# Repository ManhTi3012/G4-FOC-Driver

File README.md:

# ⚠️ **WARNING: PROJECT UNDER DEVELOPMENT, CHANGES WILL BE MADE**

# G4-FOC-Driver

# Liability
* The software and hardware are still in development and may contain bugs, errors, or incomplete features.
* Users are encouraged to use this software and hardware responsibly and at their own risk.

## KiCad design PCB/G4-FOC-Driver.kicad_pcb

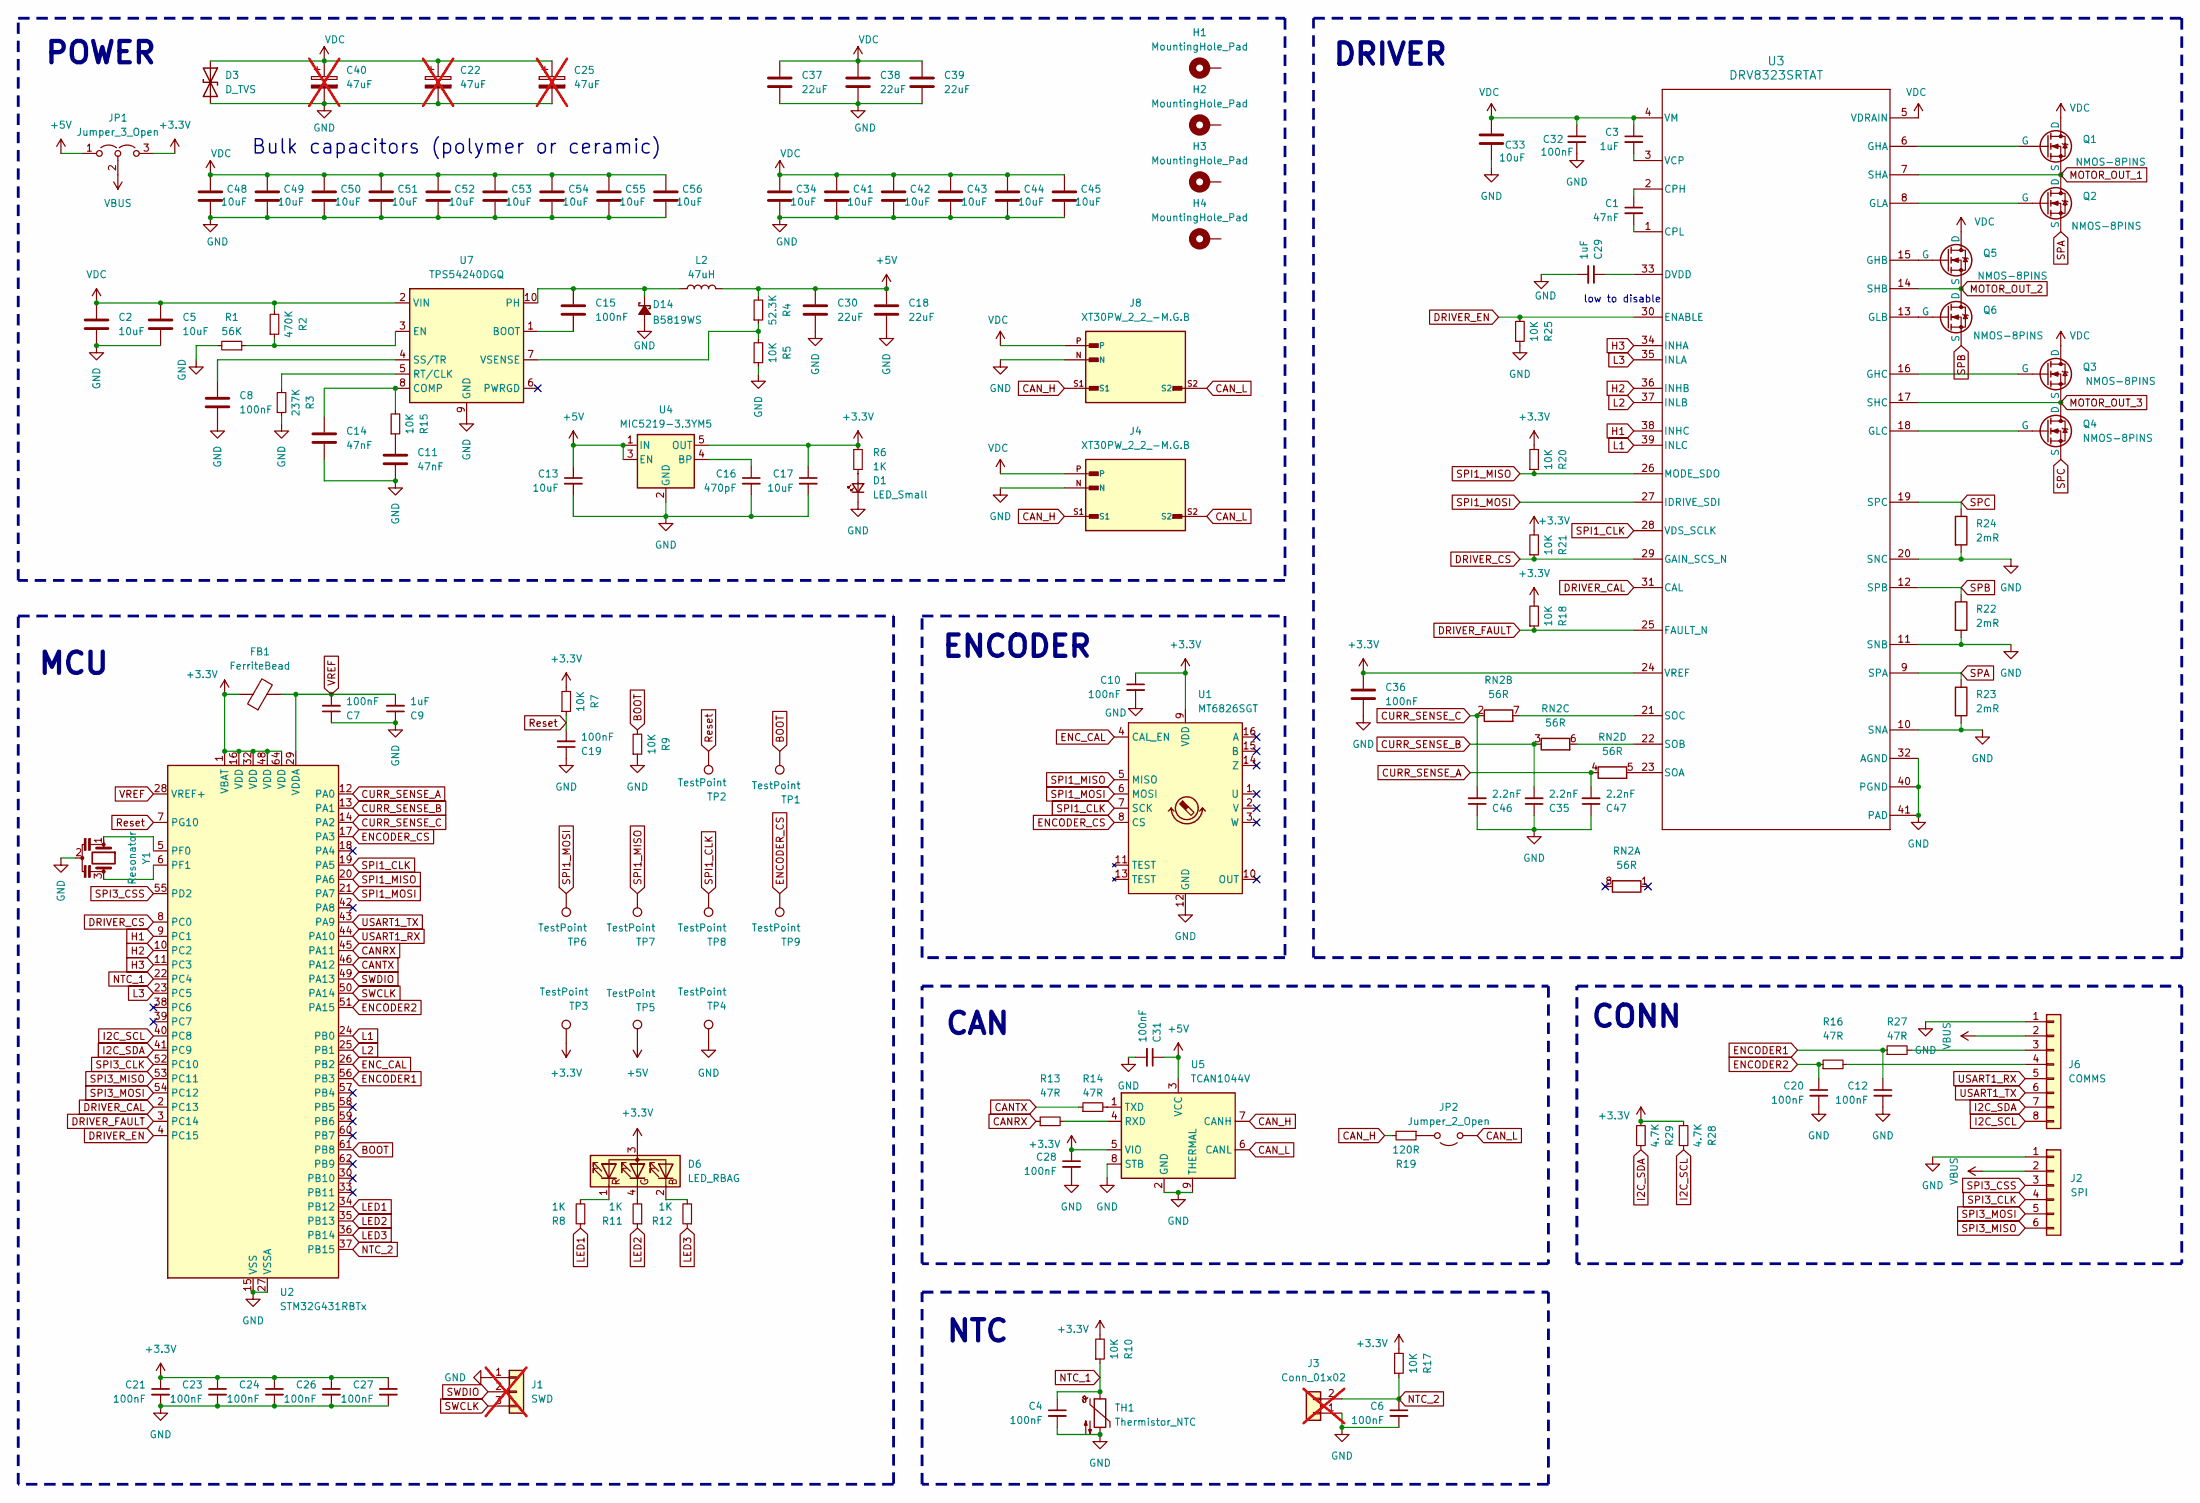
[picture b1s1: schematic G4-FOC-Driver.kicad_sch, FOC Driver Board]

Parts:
C1, C11, C14: 47nF; C_0603_1608Metric
C2, C5, C33, C34, C41, C42, C43, C44, C45, C48, C49, C50, C51, C52, C53, C54, C55, C56: 10uF; C_1206_3216Metric
C3, C9, C29: 1uF; C_0603_1608Metric
C4, C6, C7, C8, C10, C12, C15, C19, C20, C21, C23, C24, C26, C27, C28, C31, C32, C36: 100nF; C_0603_1608Metric
C13, C17: 10uF; C_0603_1608Metric
C16: 470pF; C_0603_1608Metric
C18, C30, C37, C38, C39: 22uF; C_0805_2012Metric
C22, C25, C40: 47uF; CP_Elec_6.3x5.9; not fitted
C35, C46, C47: 2.2nF; C_0603_1608Metric
D1: LED_Small; LED_0603_1608Metric
D3: D_TVS; D_SMB
D6: LED_RBAG; LED_Cree-PLCC4_2x2mm_CW
D14: B5819WS; D_0805_2012Metric
FB1: FerriteBead; L_0603_1608Metric
H1, H2, H3, H4: MountingHole_Pad; MountingHole_3.2mm_M3_Pad_Via
J1: SWD; PinHeader_1x03_P2.54mm_Vertical; not fitted
J2: SPI; JST_GH_SM06B-GHS-TB_1x06-1MP_P1.25mm_Horizontal
J3: Conn_01x02; PinHeader_1x02_P2.00mm_Vertical; not fitted
J4, J8: XT30PW_2_2_-M.G.B; AMASS_XT30PW_2_2_-M.G.B; PARTREV NA
J6: COMMS; JST_GH_SM08B-GHS-TB_1x08-1MP_P1.25mm_Horizontal
JP1: Jumper_3_Open; SolderJumper-3_P1.3mm_Open_RoundedPad1.0x1.5mm
JP2: Jumper_2_Open; SolderJumper-2_P1.3mm_Open_RoundedPad1.0x1.5mm
L2: 47uH; L_APV_ANR4020
Q1, Q2, Q3, Q4, Q5, Q6: NMOS-8PINS; PQFN-8-EP_6x5mm_P1.27mm_Generic
R1: 56K; R_0603_1608Metric
R2: 470K; R_0603_1608Metric
R3: 237K; R_0603_1608Metric
R4: 52.3K; R_0603_1608Metric
R5, R7, R9, R10, R15, R17, R18, R20, R21, R25: 10K; R_0603_1608Metric
R6, R8, R11, R12: 1K; R_0603_1608Metric
R13, R14, R16, R27: 47R; R_0603_1608Metric
R19: 120R; R_0603_1608Metric
R22, R23, R24: 2mR; R_2512_6332Metric
R28, R29: 4.7K; R_0603_1608Metric
RN2: 56R; R_Array_Convex_4x0402
TH1: Thermistor_NTC; R_0603_1608Metric
TP1, TP2, TP3, TP4, TP5, TP6, TP7, TP8, TP9: TestPoint; TestPoint_Pad_D1.0mm
U1: MT6826SGT; TSSOP-16_4.4x5mm_P0.65mm
U2: STM32G431RBTx; LQFP-64_10x10mm_P0.5mm
U3: DRV8323SRTAT; RTA0040B
U4: MIC5219-3.3YM5; SOT-23-5
U5: TCAN1044V; Texas_S-PVSON-N8_ThermalVias
U7: TPS54240DGQ; HVSSOP-10-1EP_3x3mm_P0.5mm_EP1.57x1.88mm_ThermalVias
Y1: Resonator; Resonator_SMD_Murata_CSTxExxV-3Pin_3.0x1.1mm

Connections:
+3.3V: C10.1, C17.1, C21.1, C23.1, C24.1, C26.1, C27.1, C28.1, C36.1, D6.3 (A), FB1.1, JP1.3 (B), R6.1, R7.2, R10.2, R17.2, R18.2, R20.2, R21.2, R28.2, R29.2, TP3.1, U1.9 (VDD), U2.1 (VBAT), U2.16 (VDD), U2.32 (VDD), U2.48 (VDD), U2.64 (VDD), U3.24 (VREF), U4.5 (OUT), U5.5 (VIO)
+5V: C13.1, C18.2, C30.2, C31.1, JP1.1 (A), L2.2, R4.2, TP5.1, U4.1 (IN), U4.3 (EN), U5.3 (VCC)
BOOT: R9.2, TP1.1, U2.61 (PB8)
CANRX: R13.1, U2.45 (PA11)
CANTX: R14.1, U2.46 (PA12)
CAN_H: J4.S1, J8.S1, R19.2, U5.7 (CANH)
CAN_L: J4.S2, J8.S2, JP2.1 (A), U5.6 (CANL)
CURR_SENSE_A: C47.2, RN2.4 (R4.1), U2.12 (PA0)
CURR_SENSE_B: C35.2, RN2.3 (R3.1), U2.13 (PA1)
CURR_SENSE_C: C46.2, RN2.2 (R2.1), U2.14 (PA2)
DRIVER_CAL: U2.2 (PC13), U3.31 (CAL)
DRIVER_CS: R21.1, U2.8 (PC0), U3.29 (GAIN_SCS_N)
DRIVER_EN: R25.2, U2.4 (PC15), U3.30 (ENABLE)
DRIVER_FAULT: R18.1, U2.3 (PC14), U3.25 (FAULT_N)
ENCODER1: C12.1, R27.1, U2.56 (PB3)
ENCODER2: C20.1, R16.1, U2.51 (PA15)
ENCODER_CS: TP9.1, U1.8 (CS), U2.17 (PA3)
ENC_CAL: U1.4 (CAL_EN), U2.26 (PB2)
GND: C2.1, C4.2, C5.1, C6.2, C7.1, C8.1, C9.1, C10.2, C11.1, C12.2, C13.2, C14.1, C16.2, C17.2, C18.1, C19.1, C20.2, C21.2, C22.2, C23.2, C24.2, C25.2, C26.2, C27.2, C28.2, C29.2, C30.1, C31.2, C32.2, C33.1, C34.1, C35.1, C36.2, C37.1, C38.1, C39.1, C40.2, C41.1, C42.1, C43.1, C44.1, C45.1, C46.1, C47.1, C48.1, C49.1, C50.1, C51.1, C52.1, C53.1, C54.1, C55.1, C56.1, D1.1 (K), D3.2 (A2), D14.2 (A), J1.1, J2.1, J3.1, J4.N, J6.1, J8.N, R1.2, R3.1, R5.1, R9.1, R22.2, R23.2, R24.2, R25.1, TH1.2, TP4.1, U1.12 (GND), U2.15 (VSS), U2.27 (VSSA), U2.31 (VSS), U2.47 (VSS), U2.63 (VSS), U3.10 (SNA), U3.11 (SNB), U3.20 (SNC), U3.32 (AGND), U3.40 (PGND), U3.41 (PAD), U4.2 (GND), U5.2 (GND), U5.8 (STB), U5.9 (THERMAL), U7.9 (GND), U7.11 (GND), Y1.2
H1: U2.9 (PC1), U3.38 (INHC)
H2: U2.10 (PC2), U3.36 (INHB)
H3: U2.11 (PC3), U3.34 (INHA)
I2C_SCL: J6.8, R28.1, U2.40 (PC8)
I2C_SDA: J6.7, R29.1, U2.41 (PC9)
L1: U2.24 (PB0), U3.39 (INLC)
L2: U2.25 (PB1), U3.37 (INLB)
L3: U2.23 (PC5), U3.35 (INLA)
LED1: R8.1, U2.34 (PB12)
LED2: R11.1, U2.35 (PB13)
LED3: R12.1, U2.36 (PB14)
MOTOR_OUT_1: Q1.1 (S), Q1.2 (S), Q1.3 (S), Q2.5 (D), U3.7 (SHA)
MOTOR_OUT_2: Q5.1 (S), Q5.2 (S), Q5.3 (S), Q6.5 (D), U3.14 (SHB)
MOTOR_OUT_3: Q3.1 (S), Q3.2 (S), Q3.3 (S), Q4.5 (D), U3.17 (SHC)
NTC_1: C4.1, R10.1, TH1.1, U2.22 (PC4)
NTC_2: C6.1, J3.2, R17.1, U2.37 (PB15)
unnamed: C11.2, R15.1
unnamed: D1.2 (A), R6.2
unnamed: D6.2 (BK), R12.2
unnamed: D6.4 (GK), R11.2
unnamed: D6.1 (RK), R8.2
unnamed: C15.2, D14.1 (K), L2.1, U7.10 (PH)
unnamed: J6.3, R27.2
unnamed: J6.4, R16.2
unnamed: JP2.2 (B), R19.1
unnamed: Q1.4 (G), U3.6 (GHA)
unnamed: Q2.4 (G), U3.8 (GLA)
unnamed: Q3.4 (G), U3.16 (GHC)
unnamed: Q4.4 (G), U3.18 (GLC)
unnamed: Q5.4 (G), U3.15 (GHB)
unnamed: Q6.4 (G), U3.13 (GLB)
unnamed: RN2.7 (R2.2), U3.21 (SOC)
unnamed: RN2.6 (R3.2), U3.22 (SOB)
unnamed: RN2.5 (R4.2), U3.23 (SOA)
unnamed: U2.5 (PF0), Y1.1
unnamed: U2.6 (PF1), Y1.3
unnamed: C1.1, U3.2 (CPH)
unnamed: C1.2, U3.1 (CPL)
unnamed: C29.1, U3.33 (DVDD)
unnamed: C3.2, U3.3 (VCP)
unnamed: C16.1, U4.4 (BP)
unnamed: R13.2, U5.4 (RXD)
unnamed: R14.2, U5.1 (TXD)
unnamed: C15.1, U7.1 (BOOT)
unnamed: C14.2, R15.2, U7.8 (COMP)
unnamed: R1.1, R2.1, U7.3 (EN)
unnamed: R3.2, U7.5 (RT/CLK)
unnamed: C8.2, U7.4 (SS/TR)
unnamed: R4.1, R5.2, U7.7 (VSENSE)
Reset: C19.2, R7.1, TP2.1, U2.7 (PG10)
SPA: Q2.1 (S), Q2.2 (S), Q2.3 (S), R23.1, U3.9 (SPA)
SPB: Q6.1 (S), Q6.2 (S), Q6.3 (S), R22.1, U3.12 (SPB)
SPC: Q4.1 (S), Q4.2 (S), Q4.3 (S), R24.1, U3.19 (SPC)
SPI1_CLK: TP8.1, U1.7 (SCK), U2.19 (PA5), U3.28 (VDS_SCLK)
SPI1_MISO: R20.1, TP7.1, U1.5 (MISO), U2.20 (PA6), U3.26 (MODE_SDO)
SPI1_MOSI: TP6.1, U1.6 (MOSI), U2.21 (PA7), U3.27 (IDRIVE_SDI)
SPI3_CLK: J2.4, U2.52 (PC10)
SPI3_CSS: J2.3, U2.55 (PD2)
SPI3_MISO: J2.6, U2.53 (PC11)
SPI3_MOSI: J2.5, U2.54 (PC12)
SWCLK: J1.3, U2.50 (PA14)
SWDIO: J1.2, U2.49 (PA13)
USART1_RX: J6.5, U2.44 (PA10)
USART1_TX: J6.6, U2.43 (PA9)
VBUS: J2.2, J6.2, JP1.2 (C)
VDC: C2.2, C3.1, C5.2, C22.1, C25.1, C32.1, C33.2, C34.2, C37.2, C38.2, C39.2, C40.1, C41.2, C42.2, C43.2, C44.2, C45.2, C48.2, C49.2, C50.2, C51.2, C52.2, C53.2, C54.2, C55.2, C56.2, D3.1 (A1), J4.P, J8.P, Q1.5 (D), Q3.5 (D), Q5.5 (D), R2.2, U3.4 (VM), U3.5 (VDRAIN), U7.2 (VIN)
VREF: C7.2, C9.2, FB1.2, U2.28 (VREF+), U2.29 (VDDA)

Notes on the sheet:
ENCODER
Bulk capacitors (polymer or ceramic)
MCU
NTC
POWER
low to disable
DRIVER
CAN
CONN

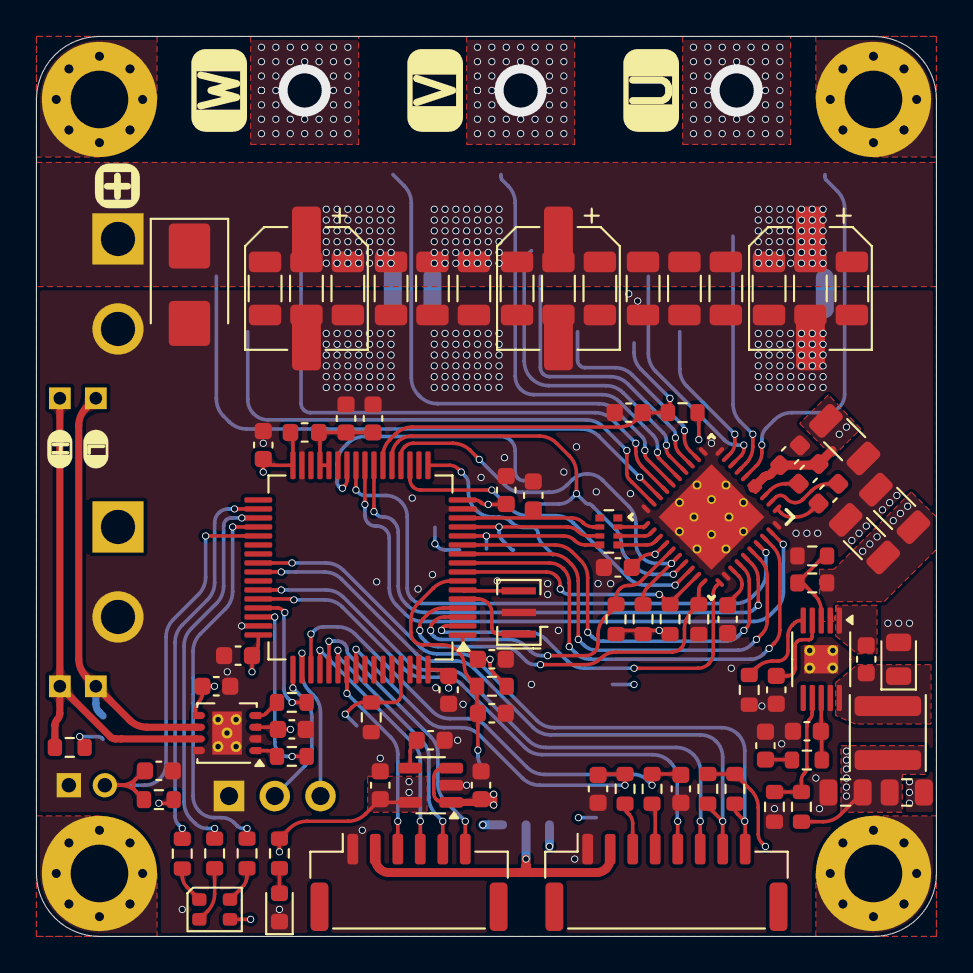
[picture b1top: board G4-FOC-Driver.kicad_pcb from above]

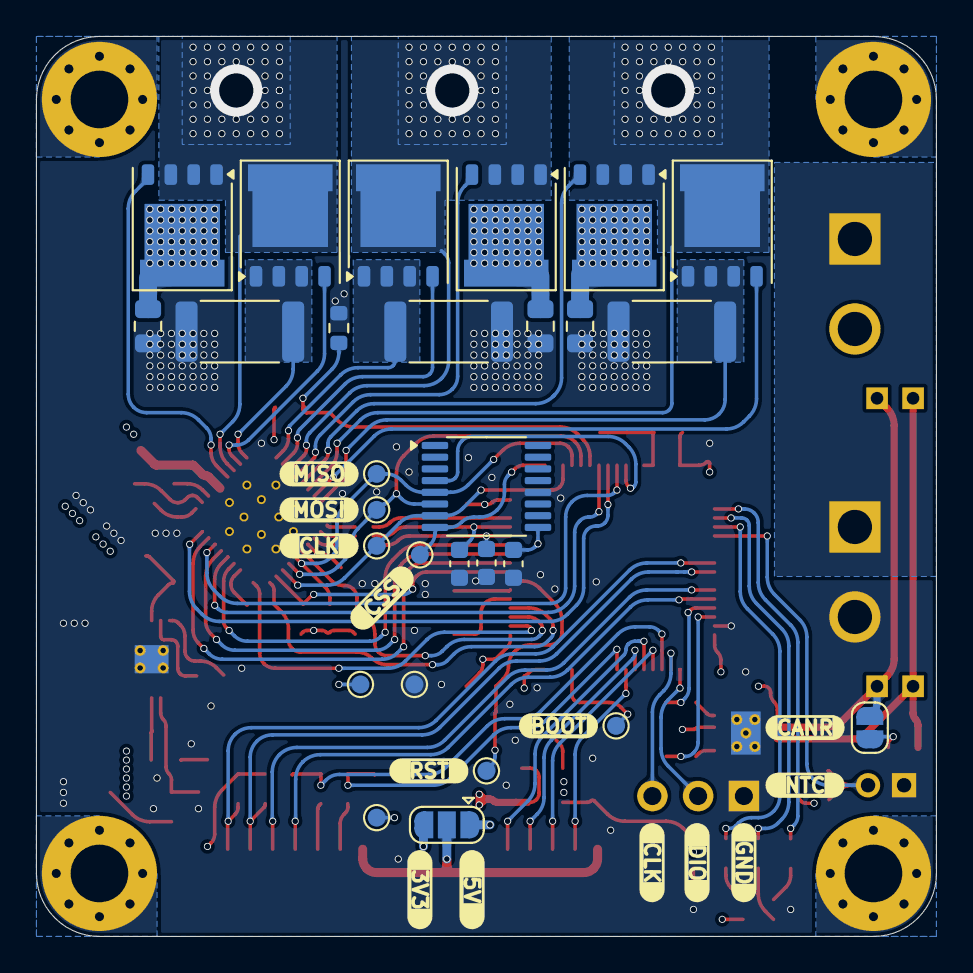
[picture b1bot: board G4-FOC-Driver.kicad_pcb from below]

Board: 4 copper layers, 50.0 x 50.0 mm, 126 parts (30 on the bottom side), 86 nets.

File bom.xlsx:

# | Value | Qty | DNP | Footprint | Pack Size | Pack Price | Currency | COST PER DEVICE | BULK COST |  | CNY to VND | 3.9
1 | 47nF | 1 |  | Capacitor_SMD:C_0603_1608Metric | 100 | 3 | CNY | 0.11699999999999999 | 11.7 |  | TOTAL COST PER DEVICE | 258.00100000000003
2 | 10uF | 18 |  | Capacitor_SMD:C_1206_3216Metric | 100 | 15 | CNY | 10.53 | 58.5 |  | MINIMUM COST | 1325.7999999999995
3 | 1uF | 3 |  | Capacitor_SMD:C_0603_1608Metric | 100 | 3 | CNY | 0.35099999999999998 | 11.7 |  | NUMBER OF DEVICEs | 5
4 | 100nF | 20 |  | Capacitor_SMD:C_0603_1608Metric | 100 | 3 | CNY | 2.34 | 11.7 |  | TOTAL COST | 1988.7999999999997
5 | 10uF | 2 |  | Capacitor_SMD:C_0603_1608Metric | 100 | 5 | CNY | 0.39 | 19.5
6 | 470pF | 1 |  | Capacitor_SMD:C_0603_1608Metric | 100 | 5 | CNY | 0.19500000000000001 | 19.5
7 | 22uF | 5 |  | Capacitor_SMD:C_0805_2012Metric | 100 | 5 | CNY | 0.97500000000000009 | 19.5
8 | 47uF | 3 | DNP | Capacitor_SMD:CP_Elec_6.3x5.9 | 10 | 6 | CNY
9 | 2.2nF | 3 |  | Capacitor_SMD:C_0603_1608Metric | 100 | 5 | CNY | 0.58499999999999996 | 19.5
10 | LED_Small | 1 |  | LED_SMD:LED_0603_1608Metric | 300 | 5 | CNY | 6.5000000000000002E-2 | 19.5
11 | D_TVS | 1 |  | Diode_SMD:D_SMB | 10 | 6 | CNY | 2.34 | 23.4
12 | LED_RBAG | 1 |  | LED_SMD:LED_Cree-PLCC4_2x2mm_CW | 100 | 6 | CNY | 0.23399999999999999 | 23.4
13 | B5819WS | 1 |  | Diode_SMD:D_0805_2012Metric | 200 | 10 | CNY | 0.19500000000000001 | 39
14 | FerriteBead | 1 |  | Inductor_SMD:L_0603_1608Metric | 100 | 4 | CNY | 0.156 | 15.6
15 | SPI | 1 |  | Connector_JST:JST_GH_SM06B-GHS-TB_1x06-1MP_P1.25mm_Horizontal | 20 | 30 |  | 1.5 | 30
16 | XT30PW_2_2_-M.G.B | 2 |  | XT30PW_2_2_-M.G.B:AMASS_XT30PW_2_2_-M.G.B | 10 | 40 | CNY | 31.200000000000003 | 156
17 | COMMS | 1 |  | Connector_JST:JST_GH_SM08B-GHS-TB_1x08-1MP_P1.25mm_Horizontal | 20 | 40 |  | 2 | 40
18 | 47uH | 1 |  | Inductor_SMD:L_APV_ANR4020 | 10 | 7 | CNY | 2.7300000000000004 | 27.3
19 | NMOS-8PINS | 6 |  | Package_DFN_QFN:PQFN-8-EP_6x5mm_P1.27mm_Generic | 150 | 90 | CNY | 14.040000000000001 | 351
20 | 56K | 1 |  | Resistor_SMD:R_0603_1608Metric | 50 | 1 | CNY | 7.8E-2 | 3.9
21 | 470K | 1 |  | Resistor_SMD:R_0603_1608Metric | 50 | 1 | CNY | 7.8E-2 | 3.9
22 | 237K | 1 |  | Resistor_SMD:R_0603_1608Metric | 50 | 1 | CNY | 7.8E-2 | 3.9
23 | 52.3K | 1 |  | Resistor_SMD:R_0603_1608Metric | 50 | 1 | CNY | 7.8E-2 | 3.9
24 | 10K | 9 |  | Resistor_SMD:R_0603_1608Metric | 100 | 1 | CNY | 0.35099999999999998 | 3.9
25 | 1K | 5 |  | Resistor_SMD:R_0603_1608Metric | 100 | 1 | CNY | 0.19500000000000001 | 3.9
26 | 47R | 4 |  | Resistor_SMD:R_0603_1608Metric | 100 | 1 | CNY | 0.156 | 3.9
27 | 120R | 1 |  | Resistor_SMD:R_0603_1608Metric | 100 | 1 | CNY | 3.9E-2 | 3.9
28 | 2mR | 3 |  | Resistor_SMD:R_2512_6332Metric | 5 | 3 | CNY | 7.02 | 11.7
29 | 4.7K | 2 |  | Resistor_SMD:R_0603_1608Metric | 100 | 1 | CNY | 7.8E-2 | 3.9
30 | 56R | 1 |  | Resistor_SMD:R_Array_Convex_4x0402 | 100 | 1 | CNY | 3.9E-2 | 3.9
31 | Thermistor_NTC | 1 |  | Resistor_SMD:R_0603_1608Metric | 50 | 6 | CNY | 0.46799999999999997 | 23.4
32 | MT6826SGT | 1 |  | Package_SO:TSSOP-16_4.4x5mm_P0.65mm | 1 | 16 | CNY | 62.4 | 62.4
33 | STM32G431RBTx | 1 |  | Package_QFP:LQFP-64_10x10mm_P0.5mm | 1 | 9 | CNY | 35.1 | 35.1
34 | DRV8323SRTAT | 1 |  | DRV8323SRTAT:RTA0040B | 1 | 11 | CNY | 42.9 | 42.9
35 | MIC5219-3.3YM5 | 1 |  | Package_TO_SOT_SMD:SOT-23-5 | 1 | 1.5 | CNY | 5.85 | 5.85
36 | TCAN1044V | 1 |  | Package_SON:Texas_S-PVSON-N8_ThermalVias | 1 | 1.5 | CNY | 5.85 | 5.85
37 | TPS54240DGQ | 1 |  | Package_SO:HVSSOP-10-1EP_3x3mm_P0.5mm_EP1.57x1.88mm_ThermalVias | 1 | 2 | CNY | 7.8 | 7.8
38 | Resonator | 1 | DNP | Crystal:Resonator_SMD_Murata_CSTxExxV-3Pin_3.0x1.1mm | 1 | 3 | CNY
39 | PCB | 1 |  |  | 10 | 50 | CNY | 19.5 | 195

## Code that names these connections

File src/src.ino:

#include <SimpleFOC.h>
#include "MagneticSensorMT6826.h"
#include "StatusLED.h"
// ===== Sensor =====
MagneticSensorMT6826 sensor(PA3);
StatusLED statusLED(PB14, PB12);

// ===== Serial =====
HardwareSerial Serial3(USART3);

// ===== Motor & Driver =====
BLDCMotor motor = BLDCMotor(20);
BLDCDriver6PWM driver = BLDCDriver6PWM(
  PC1, PB0,
  PC2, PB1,
  PC3, PC5,
  PC15
);

// ===== Commander =====
Commander command = Commander(Serial3);
void doTarget(char* cmd) { command.scalar(&motor.target, cmd); }

unsigned long long timer = 0;

void setup() {
  // ---- Serial ----
  Serial3.setTx(PA9);
  Serial3.setRx(PA10);
  Serial3.begin(115200);
  SimpleFOCDebug::enable(&Serial3);

  Serial3.println("MT6826 FOC torque test");

  // ---- Sensor ----
  sensor.init();
  motor.linkSensor(&sensor);
  Serial3.println("MT6826 ready");
  statusLED.begin();

  // ---- Driver ----
  driver.voltage_power_supply = 24.0f;
  driver.voltage_limit = 24.0f;
  driver.dead_zone = 0.05f;

  if (!driver.init()) {
    Serial3.println("Driver init failed!");
    while (1) {}
  }
  motor.linkDriver(&driver);
  Serial3.println("Driver ready!");

  // ---- Motor config ----
  motor.torque_controller = TorqueControlType::voltage;
  motor.controller = MotionControlType::angle;

  motor.voltage_limit = 24.0f;
  motor.voltage_sensor_align = 3.0f;

  // optional helpers
  motor.P_angle.P = 2.0;
  motor.P_angle.I = 0.1;
  motor.P_angle.D = 0.0;
  motor.PID_velocity.P = 0.3f;
  motor.PID_velocity.I = 2.0f;
  motor.PID_velocity.D = 0.0f;
  motor.LPF_velocity.Tf = 0.01f;
  motor.PID_velocity.output_ramp = 10.0f;

  // ---- Init ----
  motor.init();
  motor.initFOC();

  // ---- Commander ----
  command.add('T', doTarget, "target torque voltage");
  motor.useMonitoring(Serial3);

  motor.target = 3.14f;

  Serial3.println("Ready");
  Serial3.println("Try: T0.3  or  T1.0");
}

void loop() {
  if(millis() - timer > 2000){
    motor.target *= -1.0f;
    timer = millis();
  }
  motor.loopFOC();
  motor.move();
  command.run();
  statusLED.update();

  // sensor.update();
  // Serial3.println(sensor.getAngle());
}

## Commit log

2025-11-09 Layout and component change
2025-12-03 clean up schematic
2025-12-04 clean up
2025-12-04 Rename project from foc-motor-controller to G4-FOC-Driver
2026-04-28 Add SimpleFOC
